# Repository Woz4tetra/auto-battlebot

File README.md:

<div style="height: 220px; width: 100%; overflow: hidden; border-radius: 8px;">
  
</div>

<br/>

This project brings aim-assist and autonomous control to combat robots.

Driving skill in leagues like [NHRL](https://www.nhrl.io/) is often the deciding factor when hardware is similarly robust. The goal of this project is to deliver autonomous control to any radio-controlled combat robot.

Play recorded video through the full control pipeline.

## Built for Low Latency

The application is written in **C++** and uses **TensorRT** for inference.

On the Jetson Orin Nano, camera capture to motor motion is **< 60 ms**.*

Supported platforms:
- Jetson Orin NX or Orin Nano
  - JetPack 7.2 (Ubuntu 24.04, CUDA 13.2, Python 3.12) or JetPack 6.2 (Ubuntu 22.04, CUDA 12.6, Python 3.10)
- Intel x86 + NVIDIA GPU
  - Ubuntu 22
  - Ubuntu 24

## Fast Deployment

At NHRL, there is no time to set up tripod hardware across 8+ cages and calibrate fixed camera systems.

This system is fully handheld. The handheld device features:
- Jetson Orin NX
- e-CAM25 RGB camera
- USB connection to any OpenTX transmitter
- 2+ hours of battery
- 8-inch LCD display

If there is interest, I can release the BOM and parts list.

## Easy to Debug

The application uses **Foxglove** for visualization, **MCAP** for replay debugging, and ZED SDK's **SVO** format for video playback.

Live viewing goes through `viz_relay`, a small process that owns the Foxglove WebSocket server
on port 8765 and stays up across app restarts (`scripts/run_viz_relay.sh`, or the
`viz-relay.service` unit on the Jetson). Recordings use Foxglove protobuf and JSON schemas;
the layout is documented in `docs/foxglove_recording_format.md`.

The same relay serves a web dashboard (`web/`, Svelte). On the ZED Box
it is `http://<hostname>.local` over an Ethernet cable to an iPad, using the box's existing
hostname, and `install/install_dashboard_network.sh` sets up mDNS, the link-local address, and
the firewall. A box with its own screen shows the same page full screen through
`service/dashboard-kiosk.service`, a WebKitGTK window rather than a browser. On a dev box it is
`http://localhost:8080` after `scripts/build_web.sh`. Status topics
and commands are one table in `include/remote/protocol.hpp`; see `docs/plans/web_ui_plan.md`.

## Simulation and Playback Testing

To reduce regression risk, the system can replay recorded SVO files as if real hardware were connected.

It also includes a simulator for closed-loop behavior testing using [Genesis](https://genesis-embodied-ai.github.io/).

<p align="center"><video width="70%" src="docs/media/simulation-demo.webm" autoplay muted loop playsinline controls allowfullscreen width="100%"></video></p>

# Implementation

The system has 3 modes defined by configuration files:
- **Hardware**: Receives images from a real ZED 2i and sends control commands to a real OpenTX transmitter.
- **Simulation**: Receives images from simulation and sends commands over TCP to the simulator.
- **Playback**: Receives images from an SVO file; commands are generated but not transmitted.

## Engineering Highlights

The project focuses on end-to-end autonomy under real-time and real-world constraints.

- **Real-time systems:** C++17 implementation for camera, perception, filtering, navigation, and transmission.
- **Maintainable systems:** Components are swappable through interfaces and controlled by configuration.
- **ML in the loop:** TensorRT-accelerated YOLO segmentation and keypoint models run in the control pipeline.
- **Control + geometry:** Pursuit navigation with field-boundary clamping and velocity command generation.
- **Reproducibility/tooling:** Simulation harnesses, playback workflows, tests, and model-sync scripts reduce iteration risk.

## Pseudocode

[This document](docs/pseudo_code.md) describes runtime orchestration across modules.

## Repo Tour

- `src/`, `include/`: Core C++ runtime and interfaces
- `simulation/`: Genesis server and protocol bridge
- `config/`: Mode-specific TOML configurations
- `auto_battlebot/`: Shared Python library, the only importable and type-checked tree
- `training/`: Dataset building, model training, and offline scoring, one CLI per file
- `scripts/`, `install/`: Setup, build, and run workflows ([scripts/README.md](scripts/README.md))
- `firmware/`: Robot-side firmware experiments and support code
- `playground/`: Experimental work

# Setup and Install

These scripts assume you are on one of the supported hardware configurations:
- Jetson Orin NX or Orin Nano (JetPack 7.2 or JetPack 6)
- Ubuntu 22 or 24 (x86 + NVIDIA GPU with compute capability 8.7 or higher)

These are the platforms I've tested on. This repository may work on other system configurations.

This section assumes CUDA and TensorRT are already installed.

## Docker install

These commands ensure you have docker and docker-compose 2.20+ installed as well as the Nvidia docker runtime.
This assumes you have the appropriate Nvidia drivers installed already.

```bash
./install/install_docker_ubuntu.sh
sudo apt-get install -y nvidia-container-toolkit
sudo nvidia-ctk runtime configure --runtime=docker
sudo systemctl restart docker
```

This script builds the docker image:

```bash
./scripts/docker/build_image.sh
```

Once this succeeds, run the playback with this script:

```bash
./scripts/docker/run_playback.sh
```

To run unit tests, run these commands:

```bash
./scripts/docker/shell.sh
./scripts/build_and_test.sh
```

If there's an error about no engine file found, jump to this section "Creating New Engine Files."

## Docker-less install

I don't have a docker file for Jetson platforms.
For Jetson-specific setup, see [docs/jetson_setup.md](docs/jetson_setup.md).

To run SVO playback in a container instead, with ZED SDK, CUDA, and TensorRT already
pinned, see [docs/docker_playback.md](docs/docker_playback.md). That path is x86 only
and covers playback, not deployment.

To install the core application, run one of:
- `scripts/install_jetson.sh`
- `scripts/install_ubuntu_22.sh`
- `scripts/install_ubuntu_24.sh`

## Training and Python Tools

To install tools for training, firmware, and other Python workflows:

```bash
./scripts/setup_python.sh
```

## Simulation

To install and run simulation:

```bash
scripts/setup_simulation.sh
scripts/run_simulation.sh
```

## Obtaining Model Files

After running the Python tools setup script:

```bash
source ./scripts/activate_python.sh
python scripts/sync_models.py
```

The script lists model files that match your architecture. If none appear, continue to the next section.

### Creating New Engine Files

To create engine files for systems that do not have prebuilt artifacts:

For YOLO:

```bash
python training/yolo/convert_to_tensorrt.py <path to onnx file>
```

For DeepLabV3:

```bash
python training/deeplab/convert_to_tensorrt.py <path to pt file>
```

## Running the Application

To run playback mode:

```bash
./scripts/build_and_run.sh -c ./config/playback.toml
```

If installing on a new Jetson, deploy, build, and run the systemd service with:

```bash
./scripts/deploy_to_jetson.sh <host name or ip address>
```

To run unit tests:

```bash
./scripts/build_and_test.sh
```

## Code Style

There is no strict style guide yet. Running the check-and-fix script applies baseline corrections:

```bash
./scripts/lint
```

#### Footnotes

* [Crossfire has 19.5 ms of latency](https://oscarliang.com/rc-protocols/#CRSF).
  The sense-and-control loop takes ~35 ms on the Jetson Orin Nano.
  Camera image acquisition takes ~20 ms.
  Because these steps are asynchronous, they cannot be summed directly.
  The stated figure is a worst-case latency guarantee.

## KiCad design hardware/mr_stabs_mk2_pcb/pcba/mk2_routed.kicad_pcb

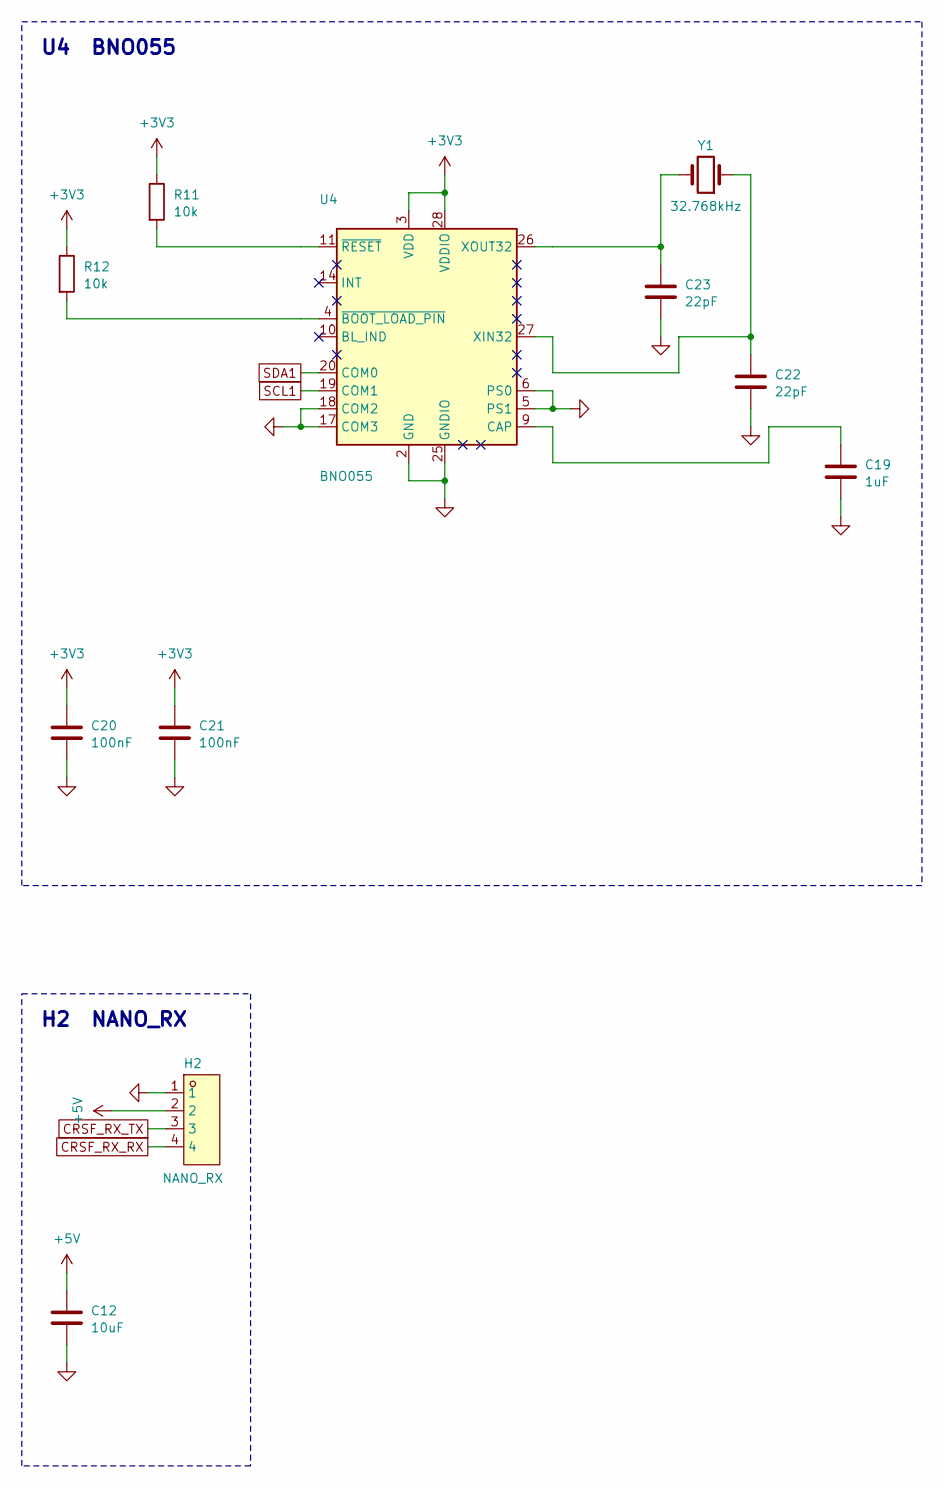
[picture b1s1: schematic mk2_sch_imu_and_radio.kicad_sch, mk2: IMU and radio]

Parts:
C12: 10uF
C19: 1uF
C20, C21: 100nF
C22, C23: 22pF
H2: NANO_RX
R11, R12: 10k
U4: BNO055
Y1: 32.768kHz

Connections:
+3V3: C20.1, C21.1, R11.1, R12.1, U4.3 (VDD), U4.28 (VDDIO); also elsewhere on the board
+5V: C12.1, H2.2; also elsewhere on the board
CRSF_RX_RX: H2.4; also elsewhere on the board
CRSF_RX_TX: H2.3; also elsewhere on the board
GND: C12.2, C19.2, C20.2, C21.2, C22.2, C23.2, H2.1, U4.2 (GND), U4.5 (PS1), U4.6 (PS0), U4.17 (COM3), U4.18 (COM2), U4.25 (GNDIO); also elsewhere on the board
IMU_BOOTLOAD: R12.2, U4.4 (~BOOT_LOAD_PIN)
IMU_CAP: C19.1, U4.9 (CAP)
IMU_RST: R11.2, U4.11 (~RESET)
SCL1: U4.19 (COM1); also elsewhere on the board
SDA1: U4.20 (COM0); also elsewhere on the board
XIN32: C22.1, U4.27 (XIN32), Y1.1
XOUT32: C23.1, U4.26 (XOUT32), Y1.2

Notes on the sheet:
U4 BNO055
H2 NANO_RX

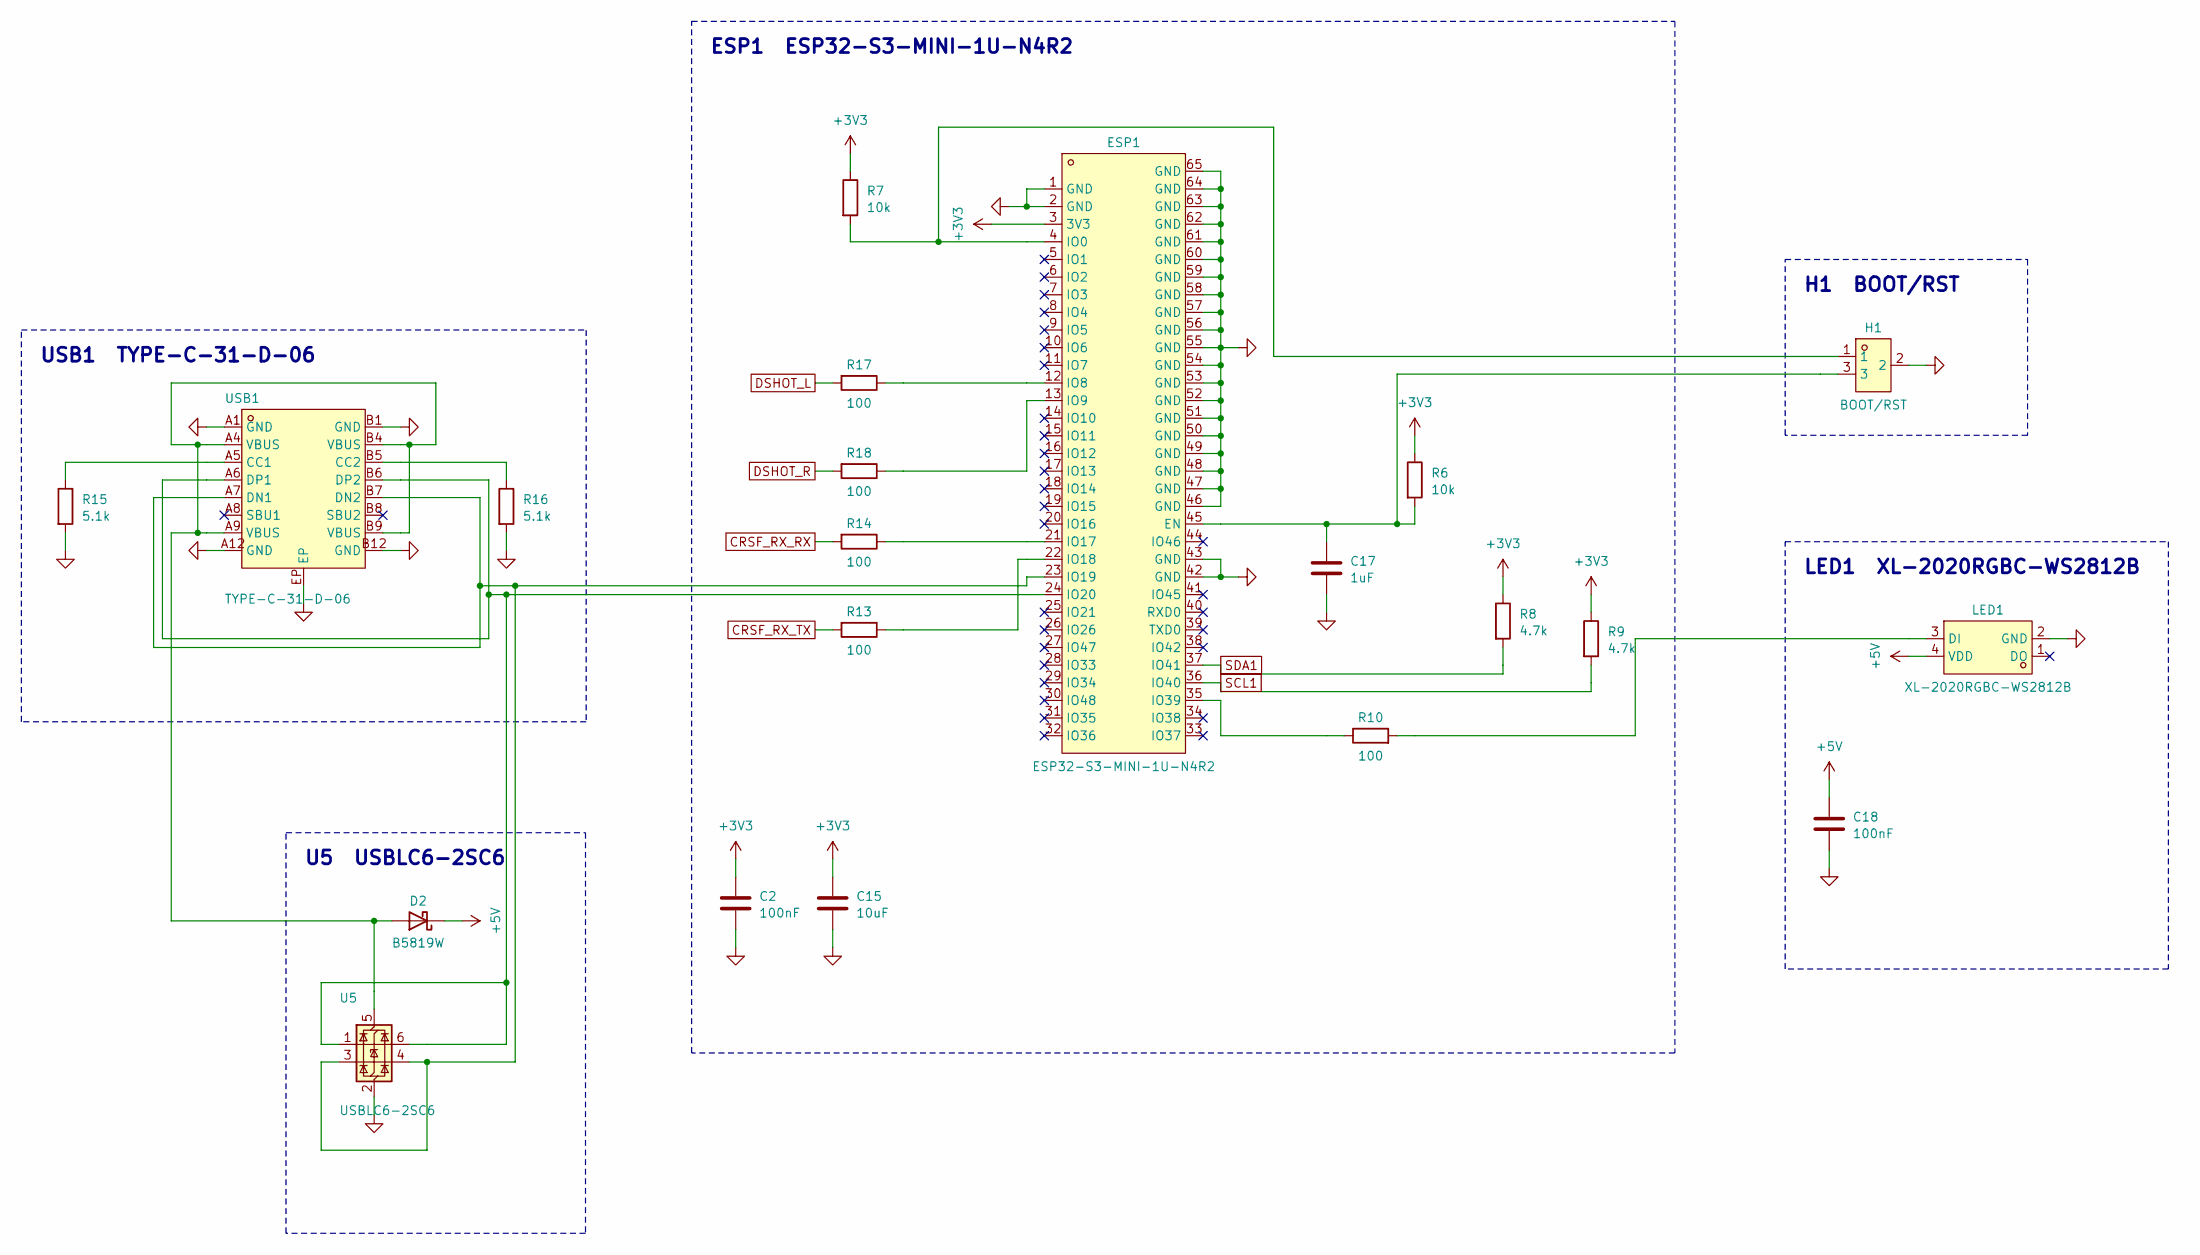
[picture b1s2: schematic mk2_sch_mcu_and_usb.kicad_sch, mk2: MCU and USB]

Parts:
C2, C18: 100nF
C15: 10uF
C17: 1uF
D2: B5819W
ESP1: ESP32-S3-MINI-1U-N4R2
H1: BOOT/RST
LED1: XL-2020RGBC-WS2812B
R6, R7: 10k
R8, R9: 4.7k
R10, R13, R14, R17, R18: 100
R15, R16: 5.1k
U5: USBLC6-2SC6
USB1: TYPE-C-31-D-06

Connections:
+3V3: C2.1, C15.1, ESP1.3 (3V3), R6.1, R7.1, R8.1, R9.1; also elsewhere on the board
+5V: C18.1, D2.1 (K), LED1.4 (VDD); also elsewhere on the board
CRSF_RX_RX: R14.2; also elsewhere on the board
CRSF_RX_TX: R13.2; also elsewhere on the board
DSHOT_L: R17.2; also elsewhere on the board
DSHOT_R: R18.2; also elsewhere on the board
EN: C17.1, ESP1.45 (EN), H1.3, R6.2
GND: C2.2, C15.2, C17.2, C18.2, ESP1.1 (GND), ESP1.2 (GND), ESP1.42 (GND), ESP1.43 (GND), ESP1.46 (GND), ESP1.47 (GND), ESP1.48 (GND), ESP1.49 (GND), ESP1.50 (GND), ESP1.51 (GND), ESP1.52 (GND), ESP1.53 (GND), ESP1.54 (GND), ESP1.55 (GND), ESP1.56 (GND), ESP1.57 (GND), ESP1.58 (GND), ESP1.59 (GND), ESP1.60 (GND), ESP1.61 (GND), ESP1.62 (GND), ESP1.63 (GND), ESP1.64 (GND), ESP1.65 (GND), H1.2, LED1.2 (GND), R15.2, R16.2, U5.2 (GND), USB1.A1 (GND), USB1.A12 (GND), USB1.B1 (GND), USB1.B12 (GND), USB1.EP; also elsewhere on the board
IO0: ESP1.4 (IO0), H1.1, R7.2
IO8: ESP1.12 (IO8), R17.1
IO9: ESP1.13 (IO9), R18.1
IO17: ESP1.21 (IO17), R14.1
IO18: ESP1.22 (IO18), R13.1
IO39: ESP1.35 (IO39), R10.1
LED_DIN: LED1.3 (DI), R10.2
SCL1: ESP1.36 (IO40), R9.2; also elsewhere on the board
SDA1: ESP1.37 (IO41), R8.2; also elsewhere on the board
USB_CC1: R15.1, USB1.A5 (CC1)
USB_CC2: R16.1, USB1.B5 (CC2)
USB_DM: ESP1.23 (IO19), U5.3 (I/O2), U5.4 (I/O2), USB1.A7 (DN1), USB1.B7 (DN2)
USB_DP: ESP1.24 (IO20), U5.1 (I/O1), U5.6 (I/O1), USB1.A6 (DP1), USB1.B6 (DP2)
VBUS_USB: D2.2 (A), U5.5 (VBUS), USB1.A4 (VBUS), USB1.A9 (VBUS), USB1.B4 (VBUS), USB1.B9 (VBUS)

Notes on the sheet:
ESP1 ESP32-S3-MINI-1U-N4R2
USB1 TYPE-C-31-D-06
U5 USBLC6-2SC6
H1 BOOT/RST
LED1 XL-2020RGBC-WS2812B

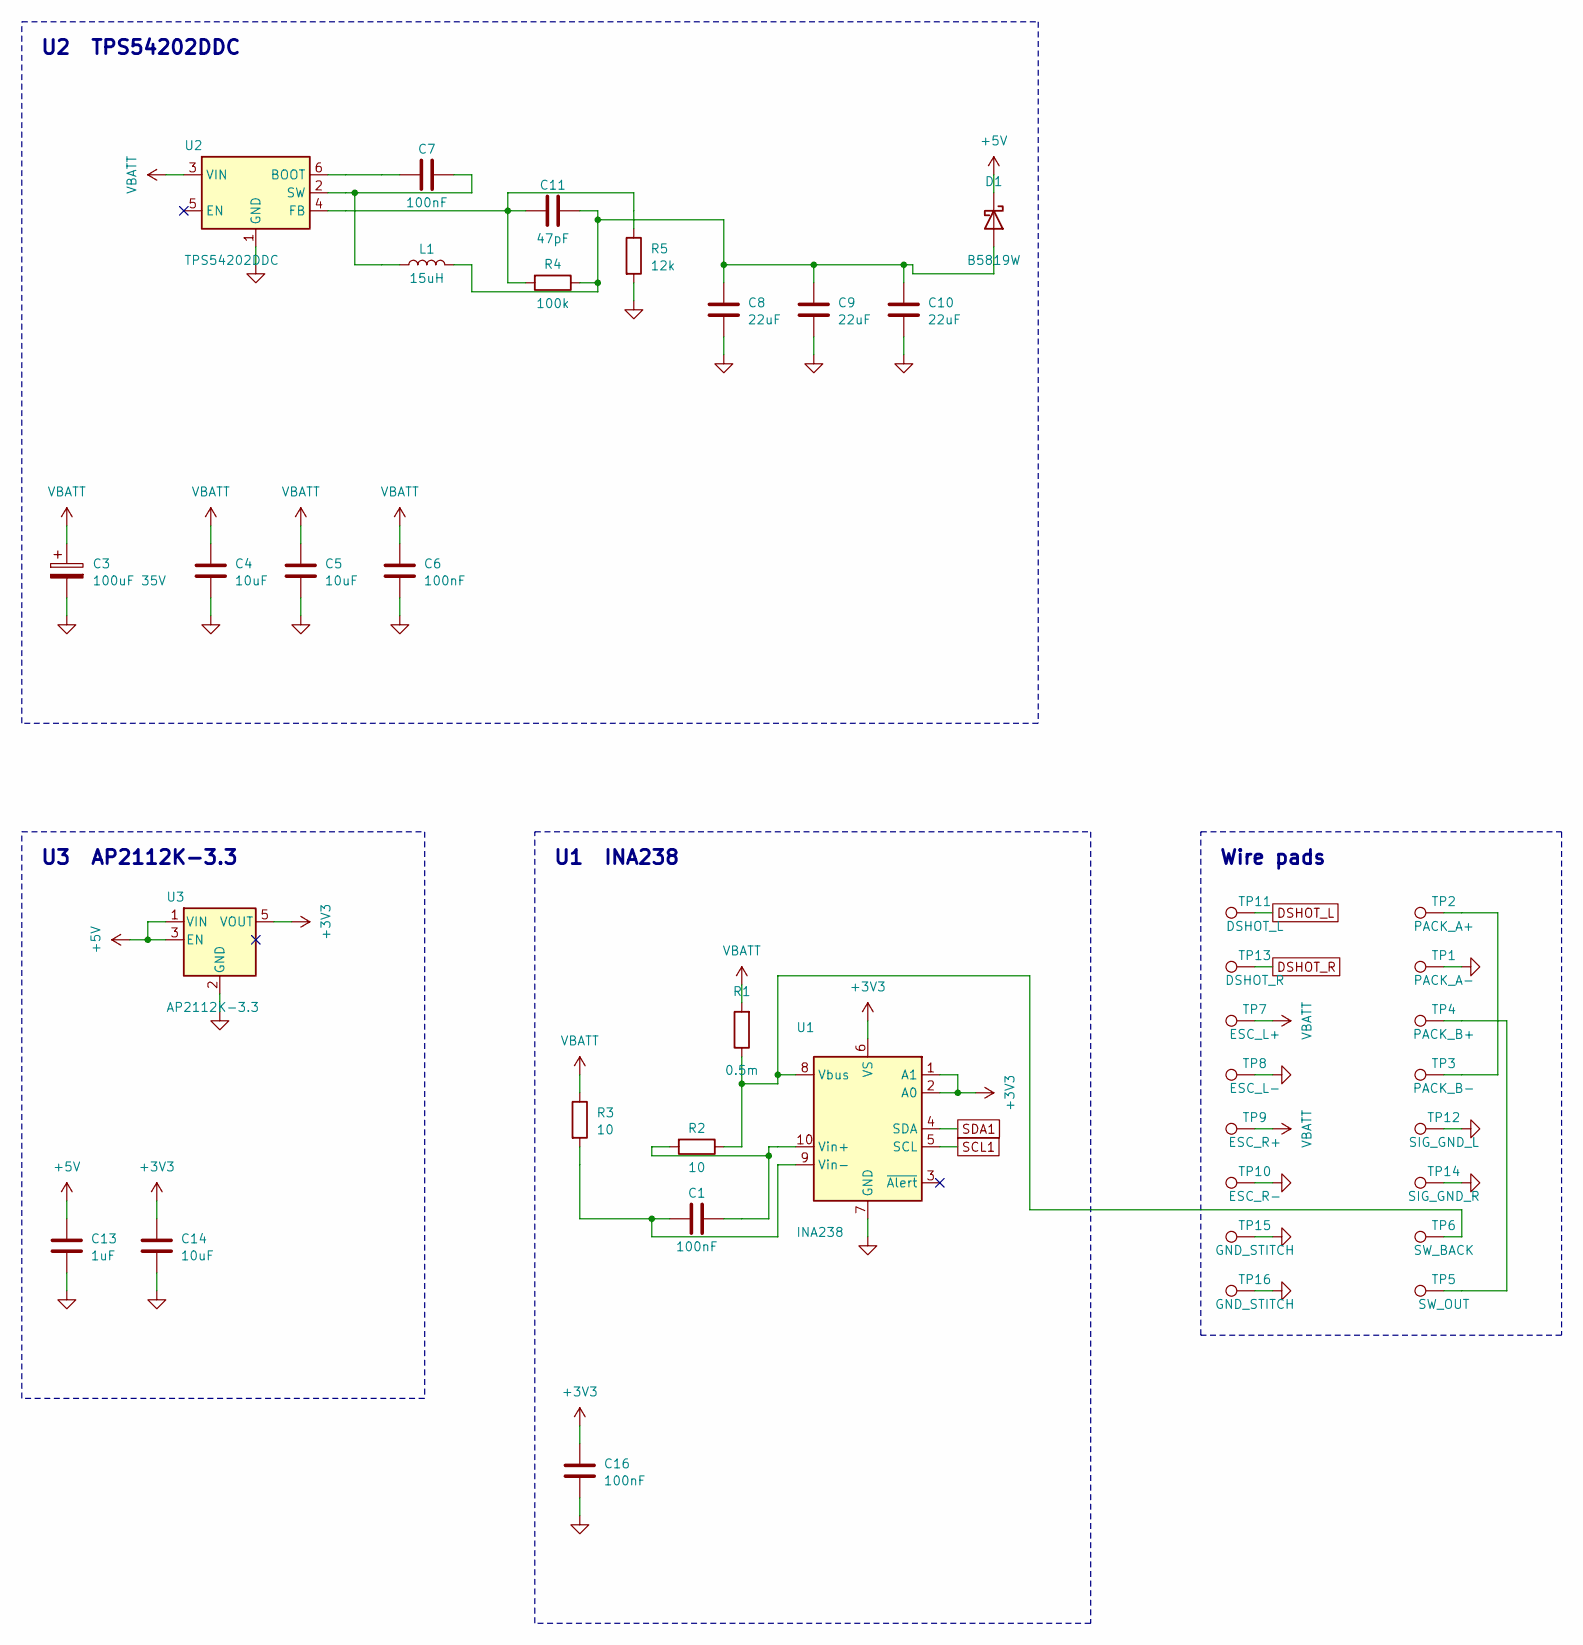
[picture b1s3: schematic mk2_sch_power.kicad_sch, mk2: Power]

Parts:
C1, C6, C7, C16: 100nF
C3: 100uF 35V
C4, C5, C14: 10uF
C8, C9, C10: 22uF
C11: 47pF
C13: 1uF
D1: B5819W
L1: 15uH
R1: 0.5m
R2, R3: 10
R4: 100k
R5: 12k
TP1: PACK_A-
TP2: PACK_A+
TP3: PACK_B-
TP4: PACK_B+
TP5: SW_OUT
TP6: SW_BACK
TP7: ESC_L+
TP8: ESC_L-
TP9: ESC_R+
TP10: ESC_R-
TP11: DSHOT_L
TP12: SIG_GND_L
TP13: DSHOT_R
TP14: SIG_GND_R
TP15, TP16: GND_STITCH
U1: INA238
U2: TPS54202DDC
U3: AP2112K-3.3

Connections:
+3V3: C14.1, C16.1, U1.1 (A1), U1.2 (A0), U1.6 (VS), U3.5 (VOUT); also elsewhere on the board
+5V: C13.1, D1.1 (K), U3.1 (VIN), U3.3 (EN); also elsewhere on the board
BAT_IN: R1.1, R2.1, TP6.1, U1.8 (Vbus)
BUCK_BOOT: C7.1, U2.6 (BOOT)
DSHOT_L: TP11.1; also elsewhere on the board
DSHOT_R: TP13.1; also elsewhere on the board
FB: C11.2, R4.2, R5.1, U2.4 (FB)
GND: C3.2, C4.2, C5.2, C6.2, C8.2, C9.2, C10.2, C13.2, C14.2, C16.2, R5.2, TP1.1, TP8.1, TP10.1, TP12.1, TP14.1, TP15.1, TP16.1, U1.7 (GND), U2.1 (GND), U3.2 (GND); also elsewhere on the board
PACK+: TP4.1, TP5.1
PACK_MID: TP2.1, TP3.1
SCL1: U1.5 (SCL); also elsewhere on the board
SDA1: U1.4 (SDA); also elsewhere on the board
SENSE_N: C1.2, R3.2, U1.9 (Vin-)
SENSE_P: C1.1, R2.2, U1.10 (Vin+)
SW: C7.2, L1.1, U2.2 (SW)
V5_BUCK: C8.1, C9.1, C10.1, C11.1, D1.2 (A), L1.2, R4.1
VBATT: C3.1, C4.1, C5.1, C6.1, R1.2, R3.1, TP7.1, TP9.1, U2.3 (VIN)

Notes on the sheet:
U2 TPS54202DDC
U3 AP2112K-3.3
U1 INA238
Wire pads

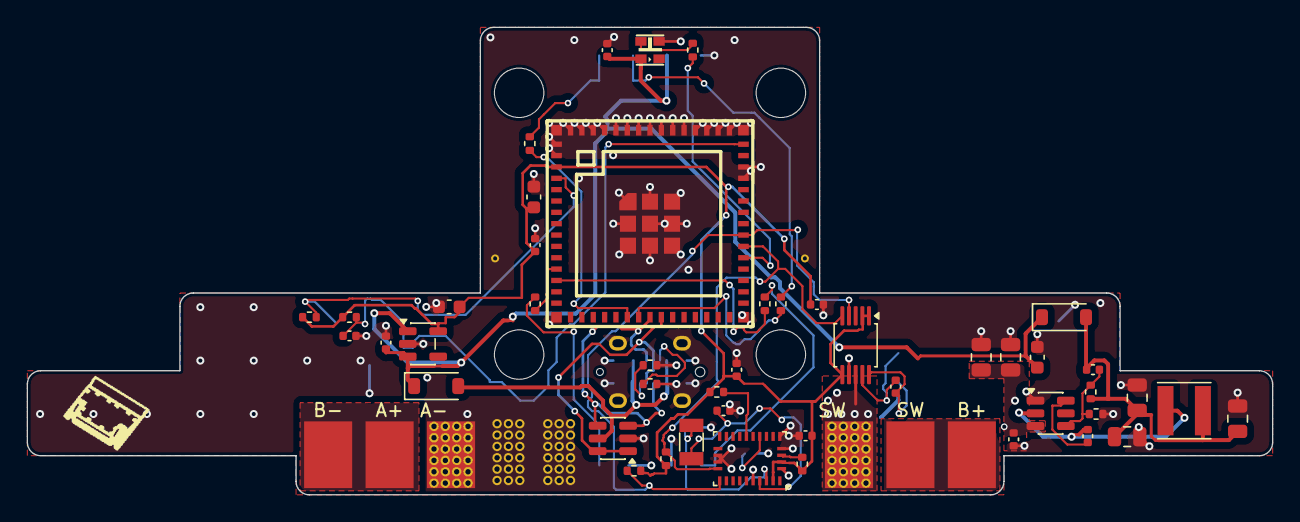
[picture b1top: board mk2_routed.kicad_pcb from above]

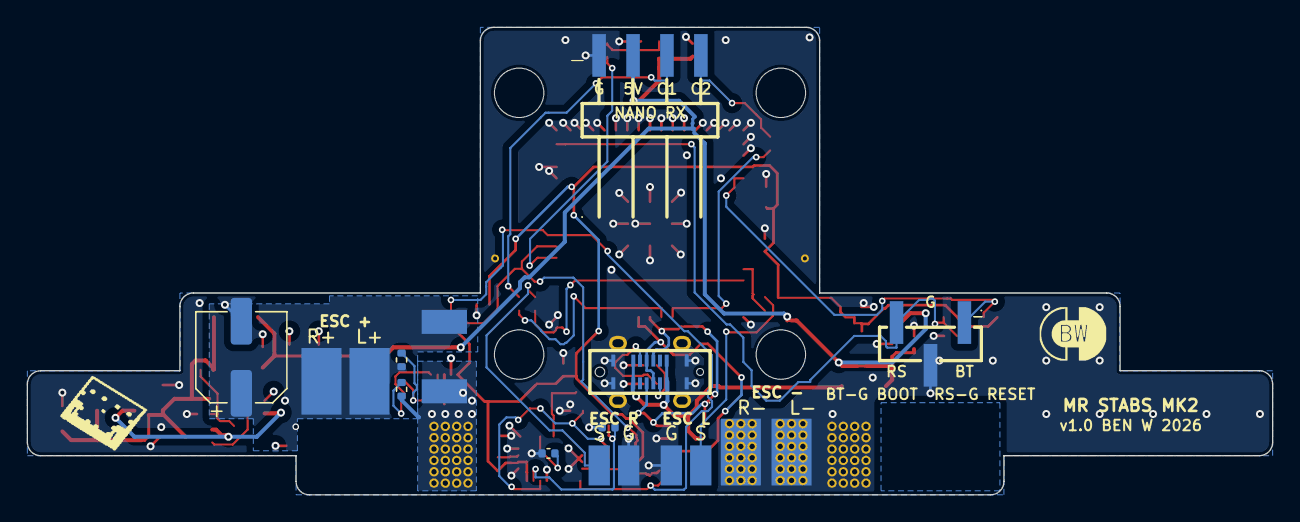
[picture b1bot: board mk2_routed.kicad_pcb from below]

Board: 4 copper layers, 93.2 x 35.0 mm, 75 parts (17 on the bottom side), 37 nets.

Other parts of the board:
H3, H4: MountingHole_L; MountingHole_3.7mm_Washer9mm_Dcut_L
H5, H6: MountingHole_R; MountingHole_3.7mm_Washer9mm_Dcut_R

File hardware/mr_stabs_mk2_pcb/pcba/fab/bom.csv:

Comment,Designator,Footprint,LCSC
100nF,"C1,C16,C18,C2,C20,C21,C7",C_0402_1005Metric,C1525
22uF,"C10,C8,C9",C_0805_2012Metric,C45783
47pF,C11,C_0402_1005Metric,C1567
10uF,"C12,C14,C15",C_0603_1608Metric,C19702
1uF,"C13,C17,C19",C_0402_1005Metric,C52923
22pF,"C22,C23",C_0402_1005Metric,C1555
100uF 35V,C3,CP_Elec_6.3x7.7,C88744
10uF,"C4,C5",C_0805_2012Metric,C15850
100nF,C6,C_0402_1005Metric,C307331
B5819W,"D1,D2",D_SOD-123,C8598
ESP32-S3-MINI-1U-N4R2,ESP1,BULETM-SMD_ESPRESSIF_ESP32-S3-MINI-1U-N8,C22356044
BOOT/RST,H1,HDR-SMD_3P-P2.54-V-M_HX-PZ2.54-1X3P-TP-YQ,C41417360
NANO_RX,H2,CONN-SMD_HX-PZ2.54-1X4P-WT,C46061677
15uH,L1,L_Taiyo-Yuden_NR-40xx,C167881
XL-2020RGBC-WS2812B,LED1,LED-SMD_4P-L2.0-W2.0-BR-1,C5349955
0.5m,R1,R_Yezhan_ASR3_2512,C469426
100,"R10,R13,R14,R17,R18",R_0402_1005Metric,C25076
10k,"R11,R12,R6,R7",R_0402_1005Metric,C25744
5.1k,"R15,R16",R_0402_1005Metric,C25905
10,"R2,R3",R_0402_1005Metric,C25077
100k,R4,R_0402_1005Metric,C25741
12k,R5,R_0402_1005Metric,C25752
4.7k,"R8,R9",R_0402_1005Metric,C25900
INA238,U1,VSSOP-10_3x3mm_P0.5mm,C2868250
TPS54202DDC,U2,SOT-23-6,C191884
AP2112K-3.3,U3,SOT-23-5,C51118
BNO055,U4,LGA-28_5.2x3.8mm_P0.5mm,C93216
USBLC6-2SC6,U5,SOT-23-6,C2687116
TYPE-C-31-D-06,USB1,USB-C-SMD_TYPE-C-31-D-06,C2689964
32.768kHz,Y1,Crystal_SMD_3215-2Pin_3.2x1.5mm,C32346
